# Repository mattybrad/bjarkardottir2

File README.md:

# Bjarkardóttir 2

A synthesizer/guitar hybrid. Somewhere between a MIDI guitar and a synthesizer. Not commercially viable. A time sink. A rabbit hole. An obsession. A mistake. An exercise in blind faith. A reason to tidy the shed. A sequel to a glass cannon.

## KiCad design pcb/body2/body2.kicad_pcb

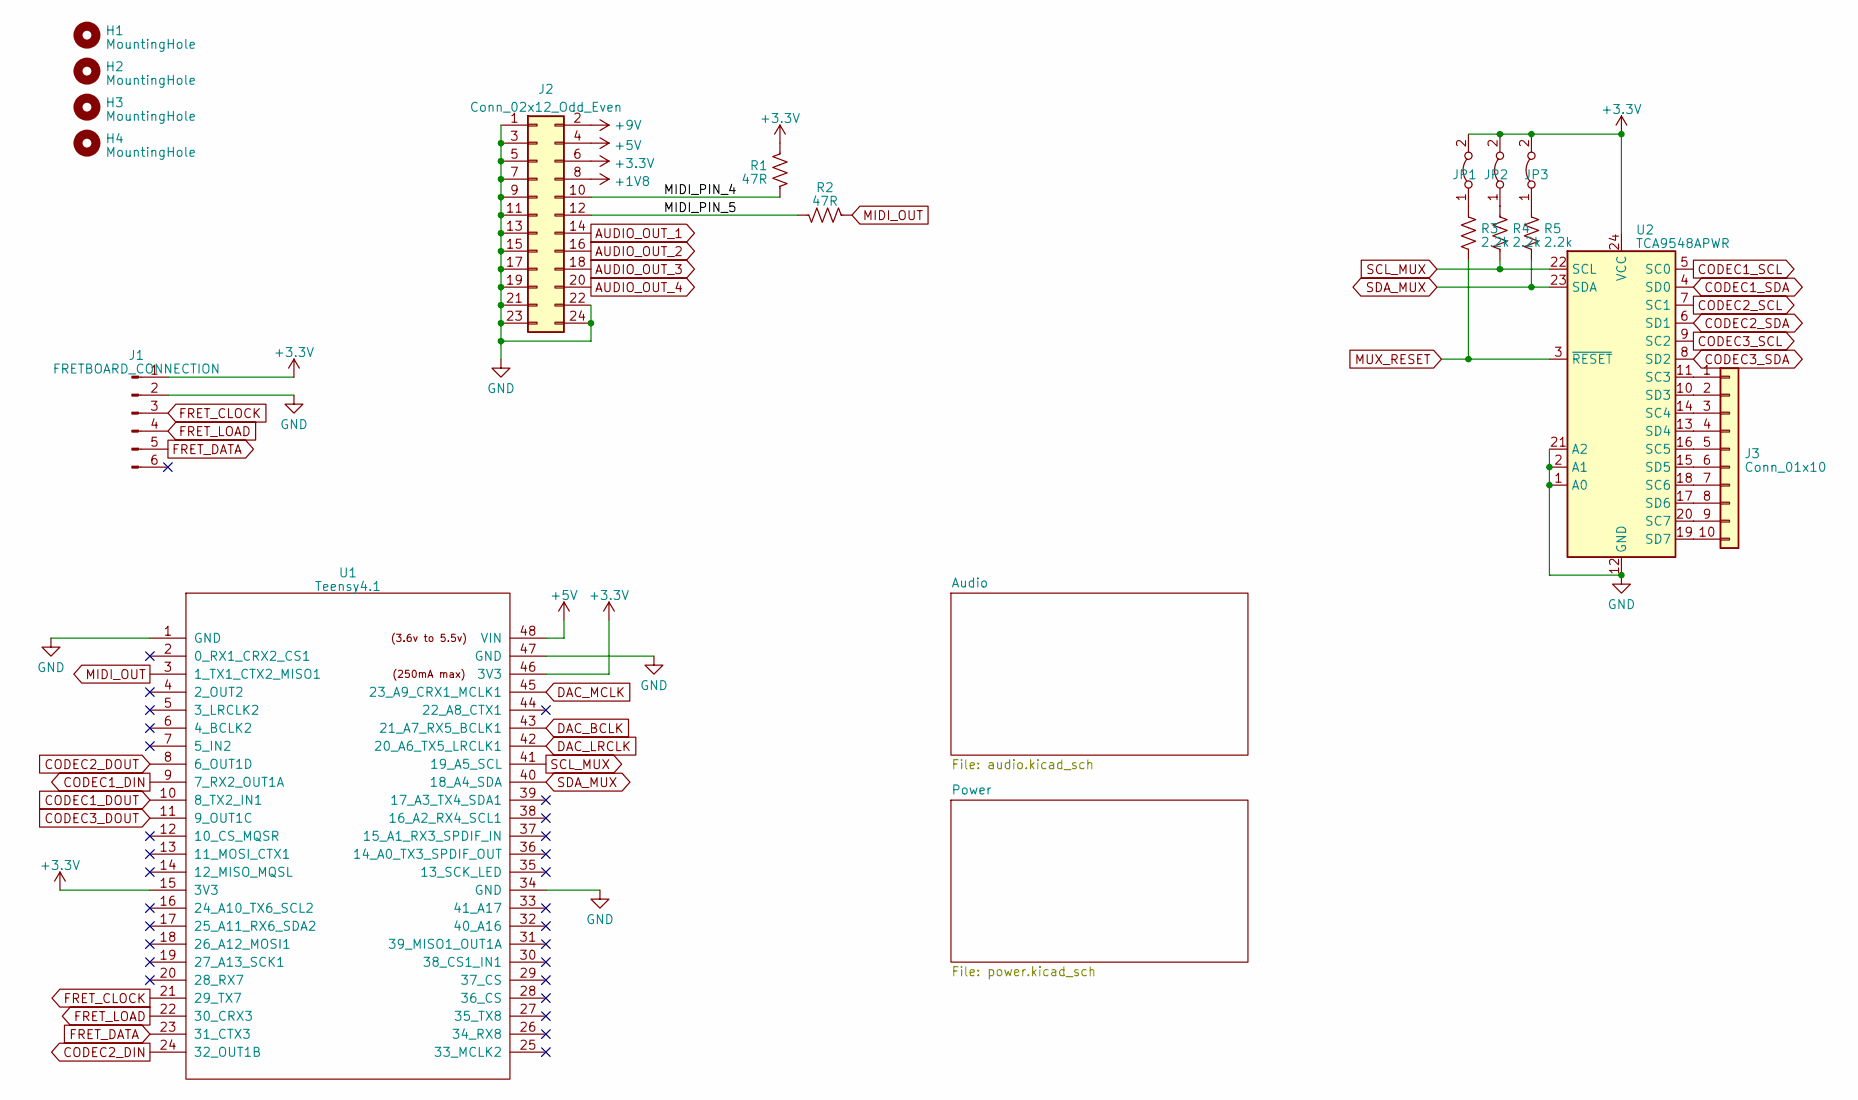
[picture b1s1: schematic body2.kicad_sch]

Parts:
H1, H2, H3, H4: MountingHole; MountingHole_3.2mm_M3
J1: FRETBOARD_CONNECTION; jst zh fretboard connector; LCSC C485355
J2: Conn_02x12_Odd_Even; PinHeader_2x12_P2.54mm_Vertical
J3: Conn_01x10; PinHeader_1x10_P1.27mm_Vertical
JP1, JP2, JP3: Jumper_2_Bridged; SolderJumper-2_P1.3mm_Bridged_Pad1.0x1.5mm
R1, R2: 47R; R_0603_1608Metric; LCSC C23182
R3, R4, R5: 2.2k; R_0603_1608Metric; LCSC C21190
U1: Teensy4.1; Teensy41_breakout
U2: TCA9548APWR; TSSOP-24_4.4x7.8mm_P0.65mm

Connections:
+1V8: J2.8; also elsewhere on the board
+3.3V: J1.1, J2.6, JP1.2 (B), JP2.2 (B), JP3.2 (B), R1.1, U1.15 (3V3), U1.46 (3V3), U2.24 (VCC); also elsewhere on the board
+5V: J2.4, U1.48 (VIN); also elsewhere on the board
+9V: J2.2; also elsewhere on the board
/MIDI_PIN_4: J2.10, R1.2
/MIDI_PIN_5: J2.12, R2.2
AUDIO_OUT_1: J2.14; also elsewhere on the board
AUDIO_OUT_2: J2.16; also elsewhere on the board
AUDIO_OUT_3: J2.18; also elsewhere on the board
AUDIO_OUT_4: J2.20; also elsewhere on the board
CODEC1_DIN: U1.9 (7_RX2_OUT1A); also elsewhere on the board
CODEC1_DOUT: U1.10 (8_TX2_IN1); also elsewhere on the board
CODEC1_SCL: U2.5 (SC0); also elsewhere on the board
CODEC1_SDA: U2.4 (SD0); also elsewhere on the board
CODEC2_DIN: U1.24 (32_OUT1B); also elsewhere on the board
CODEC2_DOUT: U1.8 (6_OUT1D); also elsewhere on the board
CODEC2_SCL: U2.7 (SC1); also elsewhere on the board
CODEC2_SDA: U2.6 (SD1); also elsewhere on the board
CODEC3_DOUT: U1.11 (9_OUT1C); also elsewhere on the board
CODEC3_SCL: U2.9 (SC2); also elsewhere on the board
CODEC3_SDA: U2.8 (SD2); also elsewhere on the board
DAC_BCLK: U1.43 (21_A7_RX5_BCLK1); also elsewhere on the board
DAC_LRCLK: U1.42 (20_A6_TX5_LRCLK1); also elsewhere on the board
DAC_MCLK: U1.45 (23_A9_CRX1_MCLK1); also elsewhere on the board
FRET_CLOCK: J1.3, U1.21 (29_TX7)
FRET_DATA: J1.5, U1.23 (31_CTX3)
FRET_LOAD: J1.4, U1.22 (30_CRX3)
GND: J1.2, J2.1, J2.3, J2.5, J2.7, J2.9, J2.11, J2.13, J2.15, J2.17, J2.19, J2.21, J2.22, J2.23, J2.24, U1.1 (GND), U1.34 (GND), U1.47 (GND), U2.1 (A0), U2.2 (A1), U2.12 (GND), U2.21 (A2); also elsewhere on the board
MIDI_OUT: R2.1, U1.3 (1_TX1_CTX2_MISO1)
MUX_RESET: R3.1, U2.3 (~RESET)
unnamed: J3.1, U2.11 (SC3)
unnamed: J3.2, U2.10 (SD3)
unnamed: J3.3, U2.14 (SC4)
unnamed: J3.4, U2.13 (SD4)
unnamed: J3.5, U2.16 (SC5)
unnamed: J3.6, U2.15 (SD5)
unnamed: J3.7, U2.18 (SC6)
unnamed: J3.8, U2.17 (SD6)
unnamed: J3.9, U2.20 (SC7)
unnamed: J3.10, U2.19 (SD7)
unnamed: JP1.1 (A), R3.2
unnamed: JP2.1 (A), R4.2
unnamed: JP3.1 (A), R5.2
SCL_MUX: R4.1, U1.41 (19_A5_SCL), U2.22 (SCL)
SDA_MUX: R5.1, U1.40 (18_A4_SDA), U2.23 (SDA)

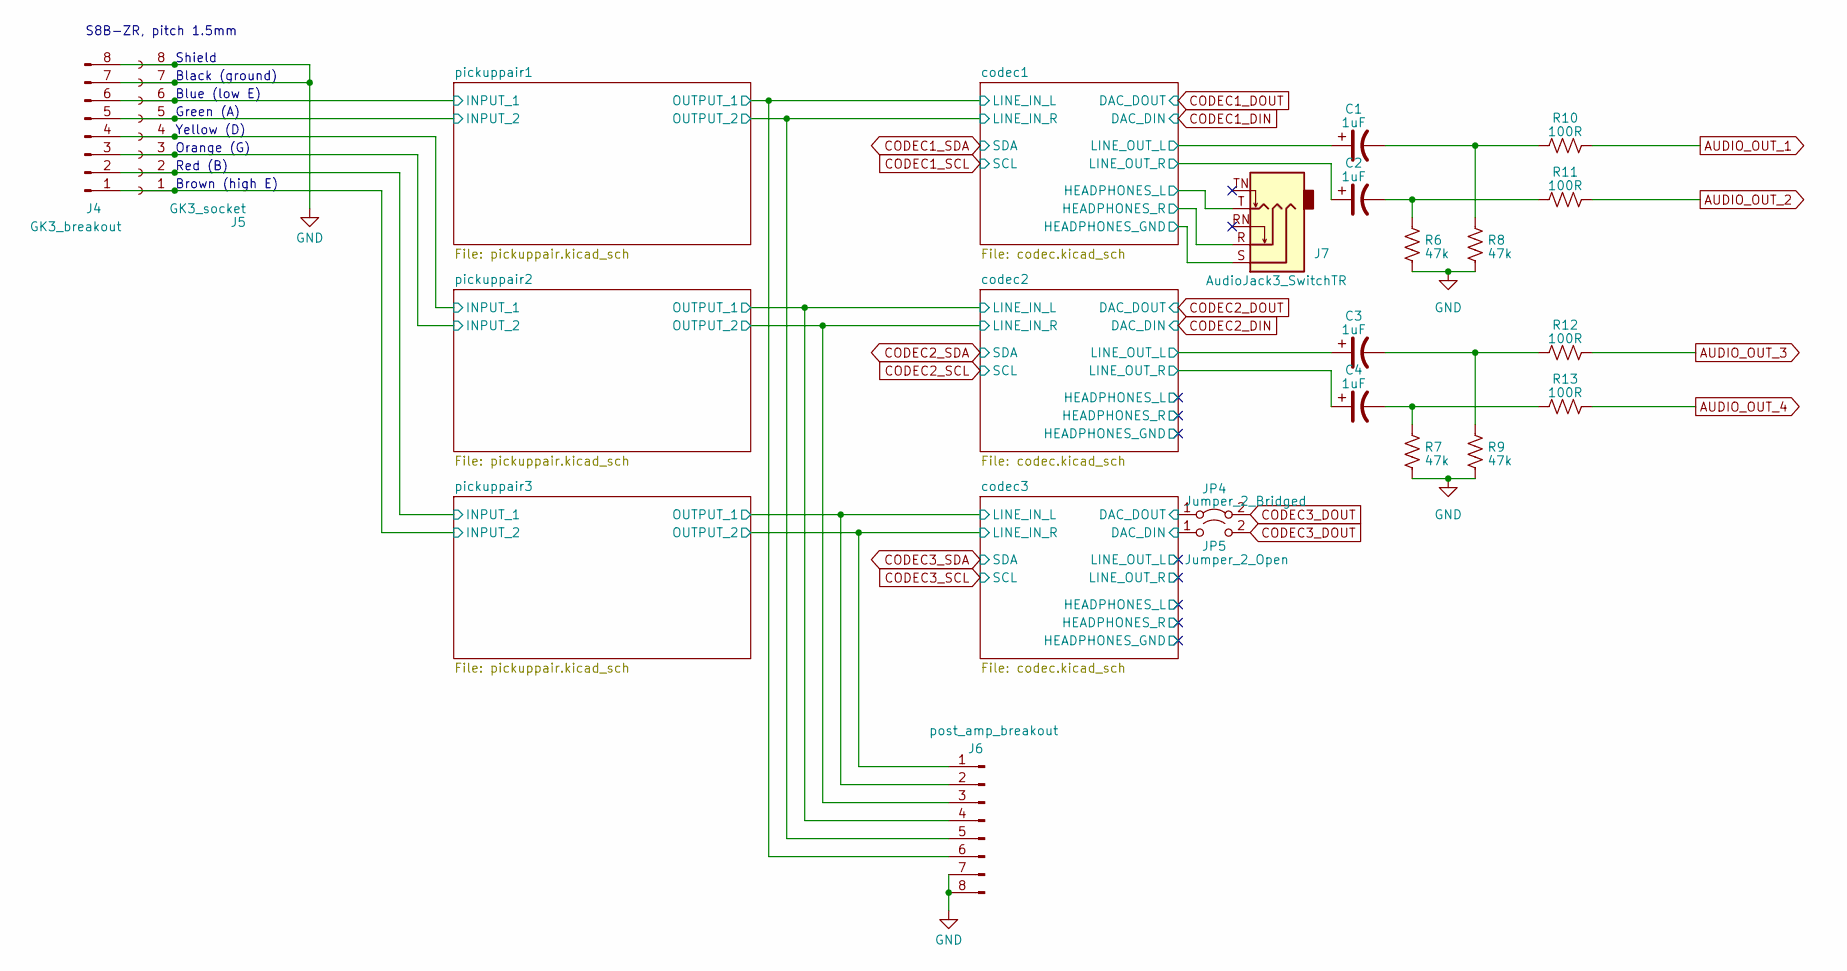
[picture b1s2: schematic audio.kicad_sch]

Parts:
C1, C3: 1uF; C_0603_1608Metric; LCSC C23630
C2, C4: 1uF; C_0603_1608Metric; LCSC C513735
J4: GK3_breakout; PinHeader_1x08_P2.54mm_Vertical
J5: GK3_socket; gk3 connector THT
J6: post_amp_breakout; PinHeader_1x08_P2.54mm_Vertical
J7: AudioJack3_SwitchTR; Jack_3.5mm_CUI_SJ1-3525N_Horizontal
JP4: Jumper_2_Bridged; SolderJumper-2_P1.3mm_Bridged_Pad1.0x1.5mm
JP5: Jumper_2_Open; SolderJumper-2_P1.3mm_Open_Pad1.0x1.5mm
R6, R7: 47k; R_0603_1608Metric; LCSC C22935
R8, R9: 47k; R_0603_1608Metric; LCSC C22976
R10, R11, R12, R13: 100R; R_0603_1608Metric; LCSC C22976

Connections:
/Audio/codec1/HEADPHONES_GND: J7.S; also elsewhere on the board
/Audio/codec1/HEADPHONES_L: J7.T; also elsewhere on the board
/Audio/codec1/HEADPHONES_R: J7.R; also elsewhere on the board
/Audio/codec1/LINE_IN_L: J6.6; also elsewhere on the board
/Audio/codec1/LINE_IN_R: J6.5; also elsewhere on the board
/Audio/codec1/LINE_OUT_L: C1.1; also elsewhere on the board
/Audio/codec1/LINE_OUT_R: C2.1; also elsewhere on the board
/Audio/codec2/LINE_IN_L: J6.4; also elsewhere on the board
/Audio/codec2/LINE_IN_R: J6.3; also elsewhere on the board
/Audio/codec2/LINE_OUT_L: C3.1; also elsewhere on the board
/Audio/codec2/LINE_OUT_R: C4.1; also elsewhere on the board
/Audio/codec3/DAC_DIN: JP5.1 (A); also elsewhere on the board
/Audio/codec3/DAC_DOUT: JP4.1 (A); also elsewhere on the board
/Audio/codec3/LINE_IN_L: J6.2; also elsewhere on the board
/Audio/codec3/LINE_IN_R: J6.1; also elsewhere on the board
/Audio/pickuppair1/INPUT_1: J4.6, J5.6; also elsewhere on the board
/Audio/pickuppair1/INPUT_2: J4.5, J5.5; also elsewhere on the board
/Audio/pickuppair2/INPUT_1: J4.4, J5.4; also elsewhere on the board
/Audio/pickuppair2/INPUT_2: J4.3, J5.3; also elsewhere on the board
/Audio/pickuppair3/INPUT_1: J4.2, J5.2; also elsewhere on the board
/Audio/pickuppair3/INPUT_2: J4.1, J5.1; also elsewhere on the board
AUDIO_OUT_1: R10.1; also elsewhere on the board
AUDIO_OUT_2: R11.1; also elsewhere on the board
AUDIO_OUT_3: R12.1; also elsewhere on the board
AUDIO_OUT_4: R13.1; also elsewhere on the board
CODEC3_DOUT: JP4.2 (B), JP5.2 (B); also elsewhere on the board
GND: J4.7, J4.8, J5.7, J5.8, J6.7, J6.8, R6.1, R7.1, R8.1, R9.1; also elsewhere on the board
unnamed: C1.2, R8.2, R10.2
unnamed: C2.2, R6.2, R11.2
unnamed: C3.2, R9.2, R12.2
unnamed: C4.2, R7.2, R13.2

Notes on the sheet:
Black (ground)
Yellow (D)
Brown (high E)
Red (B)
Green (A)
Orange (G)
S8B-ZR, pitch 1.5mm
Blue (low E)
Shield

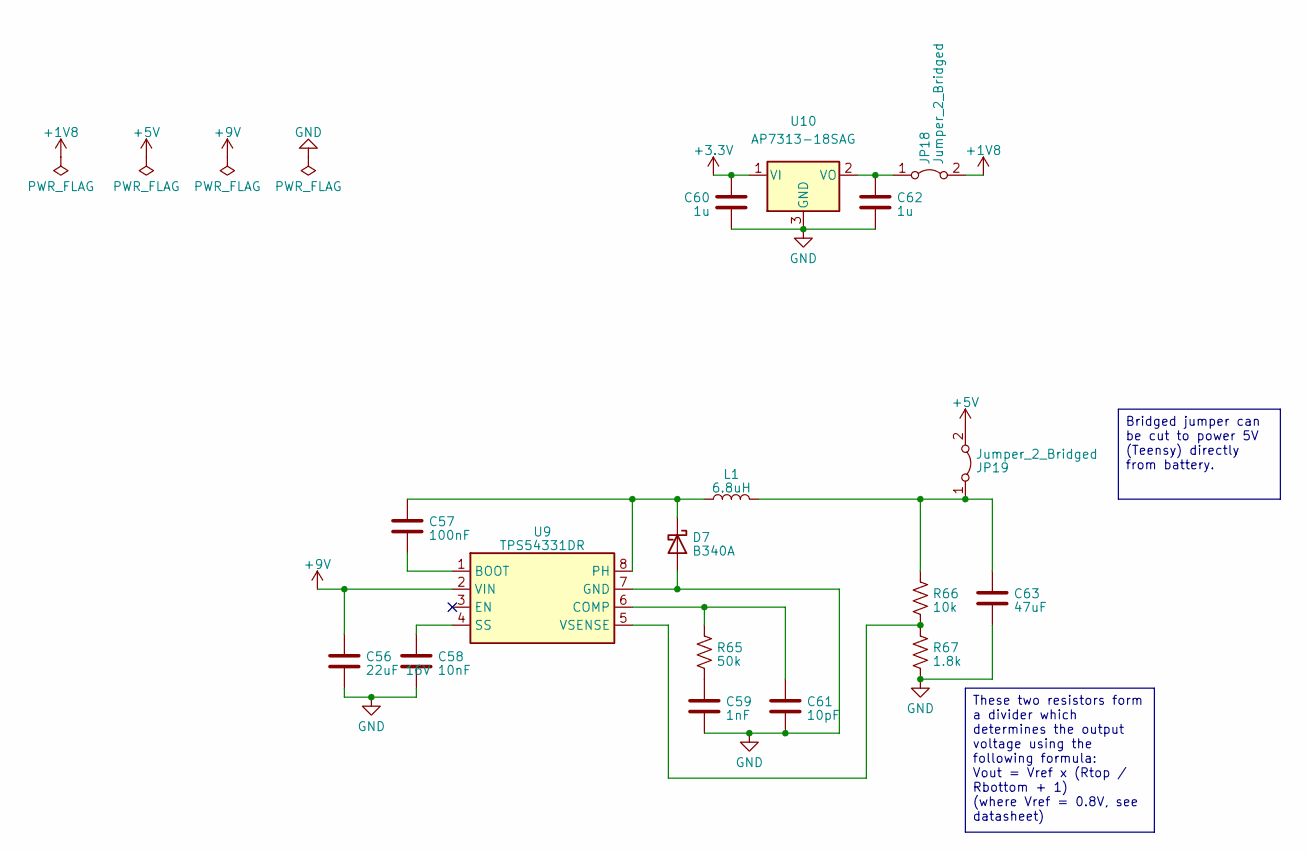
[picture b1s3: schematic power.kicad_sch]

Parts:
C56: 22uF 16V; C_0805_2012Metric
C57: 100nF; C_0603_1608Metric
C58: 10nF; C_0603_1608Metric
C59: 1nF; C_0603_1608Metric
C60, C62: 1u; C_0603_1608Metric
C61: 10pF; C_0603_1608Metric
C63: 47uF; C_1210_3225Metric
D7: B340A; D_SMA
JP18, JP19: Jumper_2_Bridged; SolderJumper-2_P1.3mm_Bridged_Pad1.0x1.5mm
L1: 6.8uH; L_Changjiang_FNR4020S
R65: 50k; R_0603_1608Metric
R66: 10k; R_0603_1608Metric
R67: 1.8k; R_0603_1608Metric
U9: TPS54331DR; SOIC-8_3.9x4.9mm_P1.27mm
U10: AP7313-18SAG; SOT-23

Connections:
+1V8: JP18.2 (B); also elsewhere on the board
+3.3V: C60.1, U10.1 (VI); also elsewhere on the board
+5V: JP19.2 (B); also elsewhere on the board
+9V: C56.1, U9.2 (VIN); also elsewhere on the board
GND: C56.2, C58.2, C59.2, C60.2, C61.2, C62.2, C63.2, D7.2 (A), R67.2, U9.7 (GND), U10.3 (GND); also elsewhere on the board
unnamed: C59.1, R65.2
unnamed: C57.1, D7.1 (K), L1.1, U9.8 (PH)
unnamed: C62.1, JP18.1 (A), U10.2 (VO)
unnamed: C63.1, JP19.1 (A), L1.2, R66.1
unnamed: C57.2, U9.1 (BOOT)
unnamed: C61.1, R65.1, U9.6 (COMP)
unnamed: C58.1, U9.4 (SS)
unnamed: R66.2, R67.1, U9.5 (VSENSE)

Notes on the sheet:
Bridged jumper can be cut to power 5V (Teensy) directly from battery.
These two resistors form a divider which determines the output voltage using the following formula: Vout = Vref x (Rtop / Rbottom + 1) (where Vref = 0.8V, see datasheet)

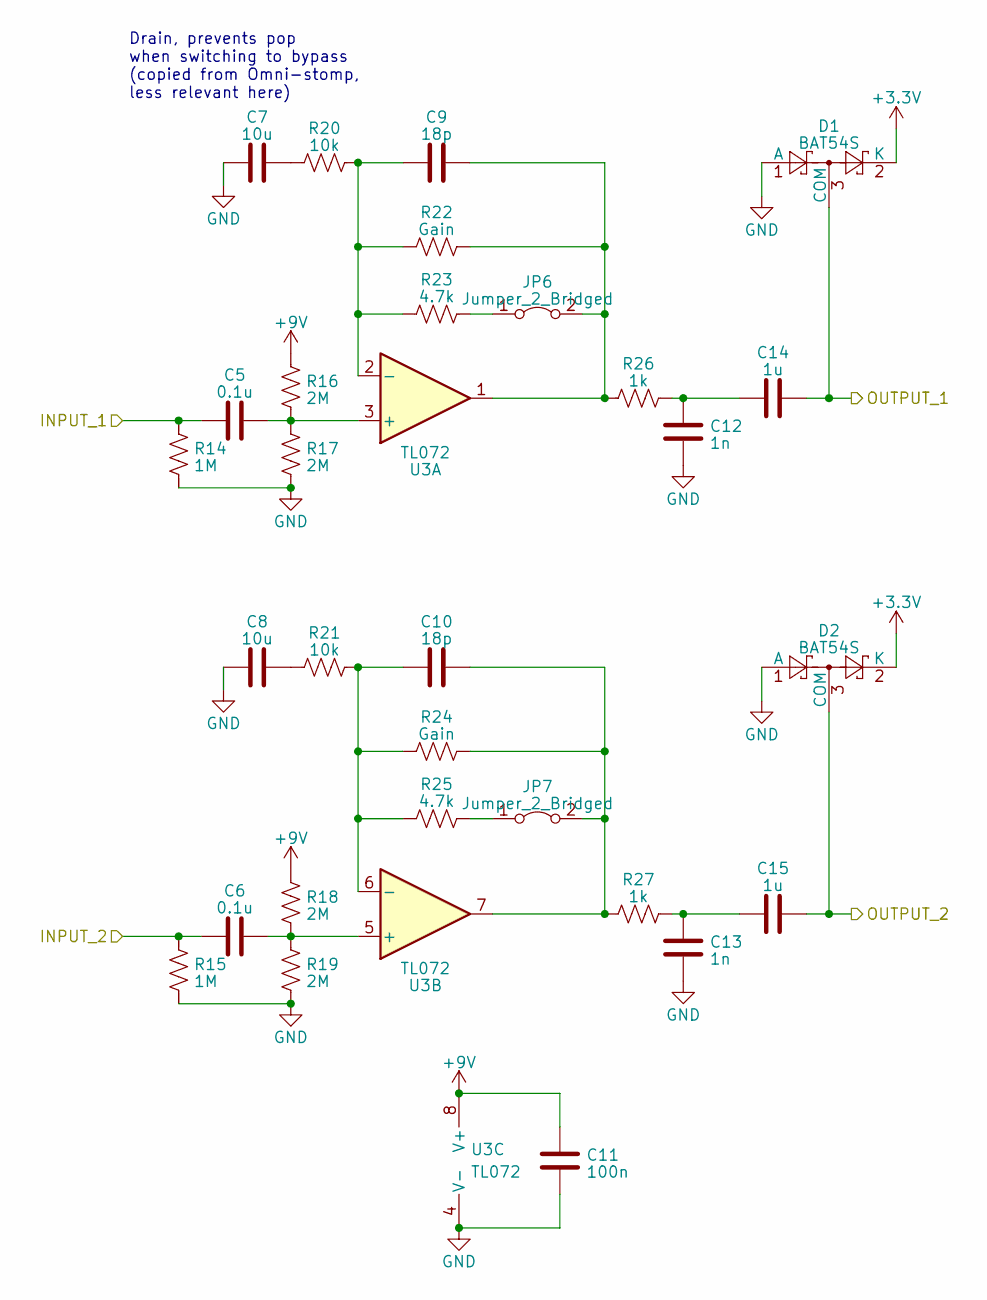
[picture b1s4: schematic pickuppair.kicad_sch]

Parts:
C5, C6: 0.1u; C_0603_1608Metric
C7, C8: 10u; C_0603_1608Metric
C9, C10: 18p; C_0603_1608Metric
C11: 100n; C_0603_1608Metric
C12, C13: 1n; C_0603_1608Metric
C14, C15: 1u; C_0603_1608Metric
D1, D2: BAT54S; SOT-23
JP6, JP7: Jumper_2_Bridged; SolderJumper-2_P1.3mm_Bridged_Pad1.0x1.5mm
R14, R15: 1M; R_0603_1608Metric
R16, R17, R18, R19: 2M; R_0603_1608Metric
R20, R21: 10k; R_0603_1608Metric
R22, R24: Gain; R_Axial_DIN0207_L6.3mm_D2.5mm_P7.62mm_Horizontal
R23, R25: 4.7k; R_0603_1608Metric
R26, R27: 1k; R_0603_1608Metric
U3: TL072; SOIC-8_3.9x4.9mm_P1.27mm

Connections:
+3.3V: D1.2 (K), D2.2 (K); also elsewhere on the board
+9V: C11.2, R16.1, R18.1, U3.8 (V+); also elsewhere on the board
/Audio/codec1/LINE_IN_L: C14.1, D1.3 (COM); also elsewhere on the board
/Audio/codec1/LINE_IN_R: C15.1, D2.3 (COM); also elsewhere on the board
/Audio/pickuppair1/INPUT_1: C5.1, R14.1; also elsewhere on the board
/Audio/pickuppair1/INPUT_2: C6.1, R15.1; also elsewhere on the board
GND: C7.1, C8.1, C11.1, C12.2, C13.2, D1.1 (A), D2.1 (A), R14.2, R15.2, R17.2, R19.2, U3.4 (V-); also elsewhere on the board
unnamed: C7.2, R20.1
unnamed: C8.2, R21.1
unnamed: C12.1, C14.2, R26.2
unnamed: C13.1, C15.2, R27.2
unnamed: JP6.1 (A), R23.2
unnamed: C9.2, JP6.2 (B), R22.2, R26.1, U3.1
unnamed: JP7.1 (A), R25.2
unnamed: C10.2, JP7.2 (B), R24.2, R27.1, U3.7
unnamed: C5.2, R16.2, R17.1, U3.3 (+)
unnamed: C9.1, R20.2, R22.1, R23.1, U3.2 (-)
unnamed: C6.2, R18.2, R19.1, U3.5 (+)
unnamed: C10.1, R21.2, R24.1, R25.1, U3.6 (-)

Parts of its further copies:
C18, C19, C29, C30: 10u; C_0603_1608Metric
C20, C21, C31, C32: 18p; C_0603_1608Metric
C22, C33: 100n; C_0603_1608Metric
C23, C24, C34, C35: 1n; C_0603_1608Metric
C25, C26, C36, C37: 1u; C_0603_1608Metric
C27, C28: 0.1u; C_0603_1608Metric
D3, D4, D5, D6: BAT54S; SOT-23
JP8, JP9, JP10, JP11: Jumper_2_Bridged; SolderJumper-2_P1.3mm_Bridged_Pad1.0x1.5mm
R28, R29, R42, R43: 1M; R_0603_1608Metric
R30, R31, R32, R33, R44, R45, R46, R47: 2M; R_0603_1608Metric
R34, R35, R48, R49: 10k; R_0603_1608Metric
R36, R38, R50, R52: Gain; R_Axial_DIN0207_L6.3mm_D2.5mm_P7.62mm_Horizontal
R37, R39, R51, R53: 4.7k; R_0603_1608Metric
R40, R41, R54, R55: 1k; R_0603_1608Metric
U4, U5: TL072; SOIC-8_3.9x4.9mm_P1.27mm

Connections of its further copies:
+3.3V: D3.2 (K), D4.2 (K), D5.2 (K), D6.2 (K); also elsewhere on the board
+9V: C22.2, C33.2, R30.1, R32.1, R44.1, R46.1, U4.8 (V+), U5.8 (V+); also elsewhere on the board
/Audio/codec2/LINE_IN_L: C25.1, D3.3 (COM); also elsewhere on the board
/Audio/codec2/LINE_IN_R: C26.1, D4.3 (COM); also elsewhere on the board
/Audio/codec3/LINE_IN_L: C36.1, D5.3 (COM); also elsewhere on the board
/Audio/codec3/LINE_IN_R: C37.1, D6.3 (COM); also elsewhere on the board
/Audio/pickuppair2/INPUT_1: R28.1; also elsewhere on the board
/Audio/pickuppair2/INPUT_2: R29.1; also elsewhere on the board
/Audio/pickuppair3/INPUT_1: C27.1, R42.1; also elsewhere on the board
/Audio/pickuppair3/INPUT_2: C28.1, R43.1; also elsewhere on the board
GND: C18.1, C19.1, C22.1, C23.2, C24.2, C29.1, C30.1, C33.1, C34.2, C35.2, D3.1 (A), D4.1 (A), D5.1 (A), D6.1 (A), R28.2, R29.2, R31.2, R33.2, R42.2, R43.2, R45.2, R47.2, U4.4 (V-), U5.4 (V-); also elsewhere on the board
unnamed: C18.2, R34.1
unnamed: C19.2, R35.1
unnamed: C23.1, C25.2, R40.2
unnamed: C24.1, C26.2, R41.2
unnamed: C29.2, R48.1
unnamed: C30.2, R49.1
unnamed: C34.1, C36.2, R54.2
unnamed: C35.1, C37.2, R55.2
unnamed: JP8.1 (A), R37.2
unnamed: C20.2, JP8.2 (B), R36.2, R40.1, U4.1
unnamed: JP9.1 (A), R39.2
unnamed: C21.2, JP9.2 (B), R38.2, R41.1, U4.7
unnamed: JP10.1 (A), R51.2
unnamed: C31.2, JP10.2 (B), R50.2, R54.1, U5.1
unnamed: JP11.1 (A), R53.2
unnamed: C32.2, JP11.2 (B), R52.2, R55.1, U5.7
unnamed 114: R30.2, R31.1, U4.3 (+); also elsewhere on the board
unnamed: C20.1, R34.2, R36.1, R37.1, U4.2 (-)
unnamed 116: R32.2, R33.1, U4.5 (+); also elsewhere on the board
unnamed: C21.1, R35.2, R38.1, R39.1, U4.6 (-)
unnamed: C27.2, R44.2, R45.1, U5.3 (+)
unnamed: C31.1, R48.2, R50.1, R51.1, U5.2 (-)
unnamed: C28.2, R46.2, R47.1, U5.5 (+)
unnamed: C32.1, R49.2, R52.1, R53.1, U5.6 (-)

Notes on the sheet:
Drain, prevents pop when switching to bypass (copied from Omni-stomp, less relevant here)

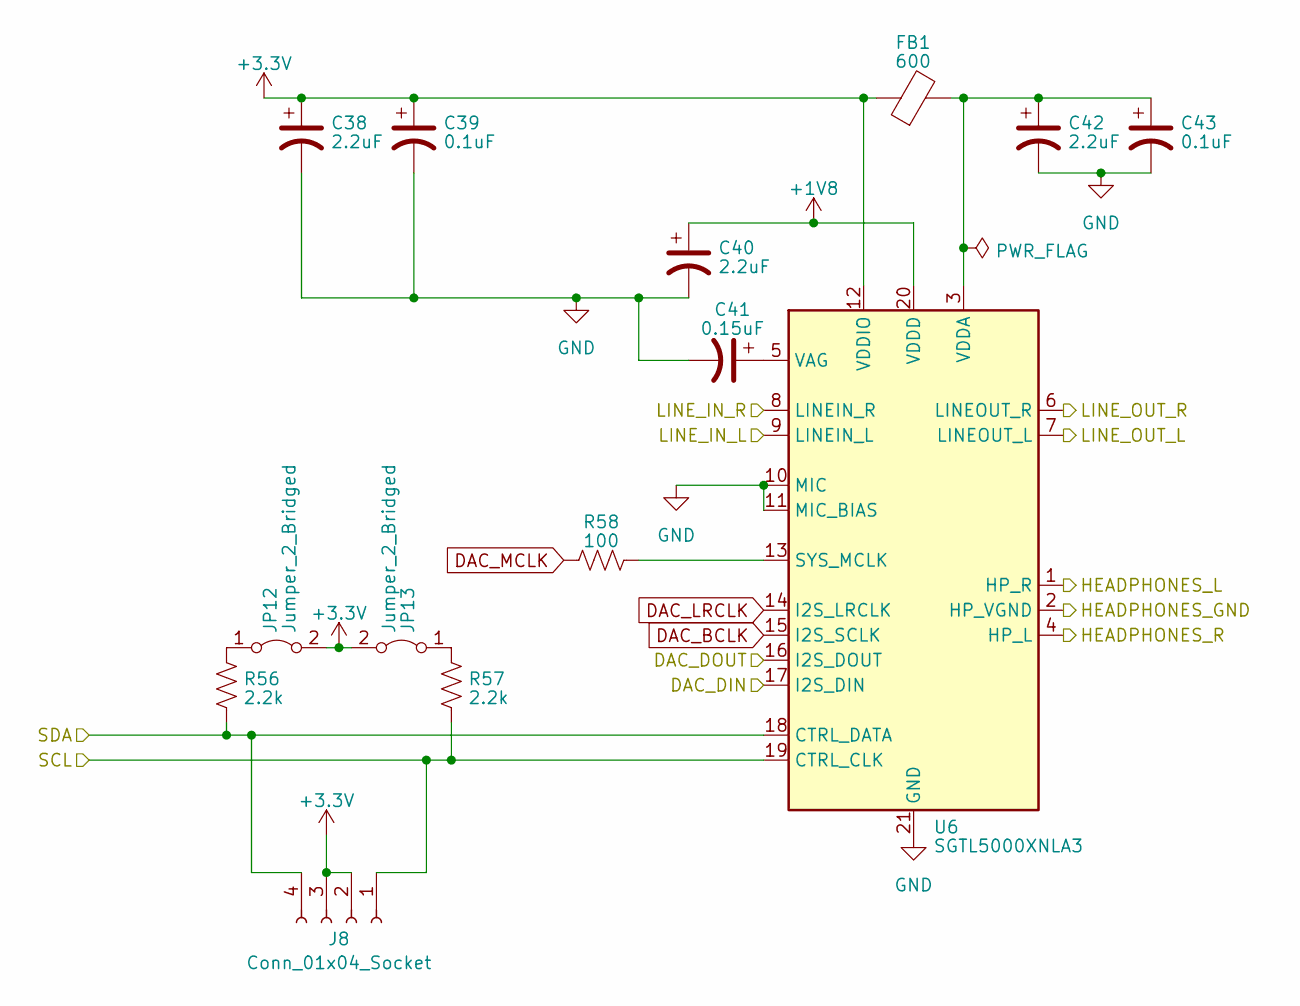
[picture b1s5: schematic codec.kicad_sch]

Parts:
C38, C40, C42: 2.2uF; C_0603_1608Metric
C39, C43: 0.1uF; C_0603_1608Metric
C41: 0.15uF; C_0603_1608Metric
FB1: 600; L_0603_1608Metric
J8: Conn_01x04_Socket; PinSocket_1x04_P1.27mm_Vertical
JP12, JP13: Jumper_2_Bridged; SolderJumper-2_P1.3mm_Bridged_Pad1.0x1.5mm
R56, R57: 2.2k; R_0603_1608Metric; LCSC C21190
R58: 100; R_0603_1608Metric
U6: SGTL5000XNLA3; QFN-20-1EP_3x3mm_P0.4mm_EP1.65x1.65mm

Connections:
+1V8: C40.1, U6.20 (VDDD); also elsewhere on the board
+3.3V: C38.1, C39.1, FB1.1, J8.2, J8.3, JP12.2 (B), JP13.2 (B), U6.12 (VDDIO); also elsewhere on the board
/Audio/codec1/HEADPHONES_GND: U6.2 (HP_VGND); also elsewhere on the board
/Audio/codec1/HEADPHONES_L: U6.1 (HP_R); also elsewhere on the board
/Audio/codec1/HEADPHONES_R: U6.4 (HP_L); also elsewhere on the board
/Audio/codec1/LINE_IN_L: U6.9 (LINEIN_L); also elsewhere on the board
/Audio/codec1/LINE_IN_R: U6.8 (LINEIN_R); also elsewhere on the board
/Audio/codec1/LINE_OUT_L: U6.7 (LINEOUT_L); also elsewhere on the board
/Audio/codec1/LINE_OUT_R: U6.6 (LINEOUT_R); also elsewhere on the board
CODEC1_DIN: U6.17 (I2S_DIN); also elsewhere on the board
CODEC1_DOUT: U6.16 (I2S_DOUT); also elsewhere on the board
CODEC1_SCL: J8.1, R57.1, U6.19 (CTRL_CLK); also elsewhere on the board
CODEC1_SDA: J8.4, R56.1, U6.18 (CTRL_DATA); also elsewhere on the board
DAC_BCLK: U6.15 (I2S_SCLK); also elsewhere on the board
DAC_LRCLK: U6.14 (I2S_LRCLK); also elsewhere on the board
DAC_MCLK: R58.2; also elsewhere on the board
GND: C38.2, C39.2, C40.2, C41.2, C42.2, C43.2, U6.10 (MIC), U6.11 (MIC_BIAS), U6.21 (GND); also elsewhere on the board
unnamed: JP12.1 (A), R56.2
unnamed: JP13.1 (A), R57.2
unnamed: R58.1, U6.13 (SYS_MCLK)
unnamed: C41.1, U6.5 (VAG)
unnamed: C42.1, C43.1, FB1.2, U6.3 (VDDA)

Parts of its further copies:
C44, C46, C48, C50, C52, C54: 2.2uF; C_0603_1608Metric
C45, C49, C51, C55: 0.1uF; C_0603_1608Metric
C47, C53: 0.15uF; C_0603_1608Metric
FB2, FB3: 600; L_0603_1608Metric
J9, J10: Conn_01x04_Socket; PinSocket_1x04_P1.27mm_Vertical
JP14, JP15, JP16, JP17: Jumper_2_Bridged; SolderJumper-2_P1.3mm_Bridged_Pad1.0x1.5mm
R59, R60, R62, R63: 2.2k; R_0603_1608Metric; LCSC C21190
R61, R64: 100; R_0603_1608Metric
U7, U8: SGTL5000XNLA3; QFN-20-1EP_3x3mm_P0.4mm_EP1.65x1.65mm

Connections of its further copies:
+1V8: C46.1, C52.1, U7.20 (VDDD), U8.20 (VDDD); also elsewhere on the board
+3.3V: C44.1, C45.1, C50.1, C51.1, FB2.1, FB3.1, J9.2, J9.3, J10.2, J10.3, JP14.2 (B), JP15.2 (B), JP16.2 (B), JP17.2 (B), U7.12 (VDDIO), U8.12 (VDDIO); also elsewhere on the board
/Audio/codec2/HEADPHONES_GND: U7.2 (HP_VGND)
/Audio/codec2/HEADPHONES_L: U7.1 (HP_R)
/Audio/codec2/HEADPHONES_R: U7.4 (HP_L)
/Audio/codec2/LINE_IN_L: U7.9 (LINEIN_L); also elsewhere on the board
/Audio/codec2/LINE_IN_R: U7.8 (LINEIN_R); also elsewhere on the board
/Audio/codec2/LINE_OUT_L: U7.7 (LINEOUT_L); also elsewhere on the board
/Audio/codec2/LINE_OUT_R: U7.6 (LINEOUT_R); also elsewhere on the board
/Audio/codec3/DAC_DIN: U8.17 (I2S_DIN); also elsewhere on the board
/Audio/codec3/DAC_DOUT: U8.16 (I2S_DOUT); also elsewhere on the board
/Audio/codec3/HEADPHONES_GND: U8.2 (HP_VGND)
/Audio/codec3/HEADPHONES_L: U8.1 (HP_R)
/Audio/codec3/HEADPHONES_R: U8.4 (HP_L)
/Audio/codec3/LINE_IN_L: U8.9 (LINEIN_L); also elsewhere on the board
/Audio/codec3/LINE_IN_R: U8.8 (LINEIN_R); also elsewhere on the board
/Audio/codec3/LINE_OUT_L: U8.7 (LINEOUT_L)
/Audio/codec3/LINE_OUT_R: U8.6 (LINEOUT_R)
CODEC2_DIN: U7.17 (I2S_DIN); also elsewhere on the board
CODEC2_DOUT: U7.16 (I2S_DOUT); also elsewhere on the board
CODEC2_SCL: J9.1, R60.1, U7.19 (CTRL_CLK); also elsewhere on the board
CODEC2_SDA: J9.4, R59.1, U7.18 (CTRL_DATA); also elsewhere on the board
CODEC3_SCL: J10.1, R63.1, U8.19 (CTRL_CLK); also elsewhere on the board
CODEC3_SDA: J10.4, R62.1, U8.18 (CTRL_DATA); also elsewhere on the board
DAC_BCLK: U7.15 (I2S_SCLK), U8.15 (I2S_SCLK); also elsewhere on the board
DAC_LRCLK: U7.14 (I2S_LRCLK), U8.14 (I2S_LRCLK); also elsewhere on the board
DAC_MCLK: R61.2, R64.2; also elsewhere on the board
GND: C44.2, C45.2, C46.2, C47.2, C48.2, C49.2, C50.2, C51.2, C52.2, C53.2, C54.2, C55.2, U7.10 (MIC), U7.11 (MIC_BIAS), U7.21 (GND), U8.10 (MIC), U8.11 (MIC_BIAS), U8.21 (GND); also elsewhere on the board
unnamed: JP14.1 (A), R59.2
unnamed: JP15.1 (A), R60.2
unnamed: JP16.1 (A), R62.2
unnamed: JP17.1 (A), R63.2
unnamed: R61.1, U7.13 (SYS_MCLK)
unnamed: C47.1, U7.5 (VAG)
unnamed: C48.1, C49.1, FB2.2, U7.3 (VDDA)
unnamed: R64.1, U8.13 (SYS_MCLK)
unnamed: C53.1, U8.5 (VAG)
unnamed: C54.1, C55.1, FB3.2, U8.3 (VDDA)

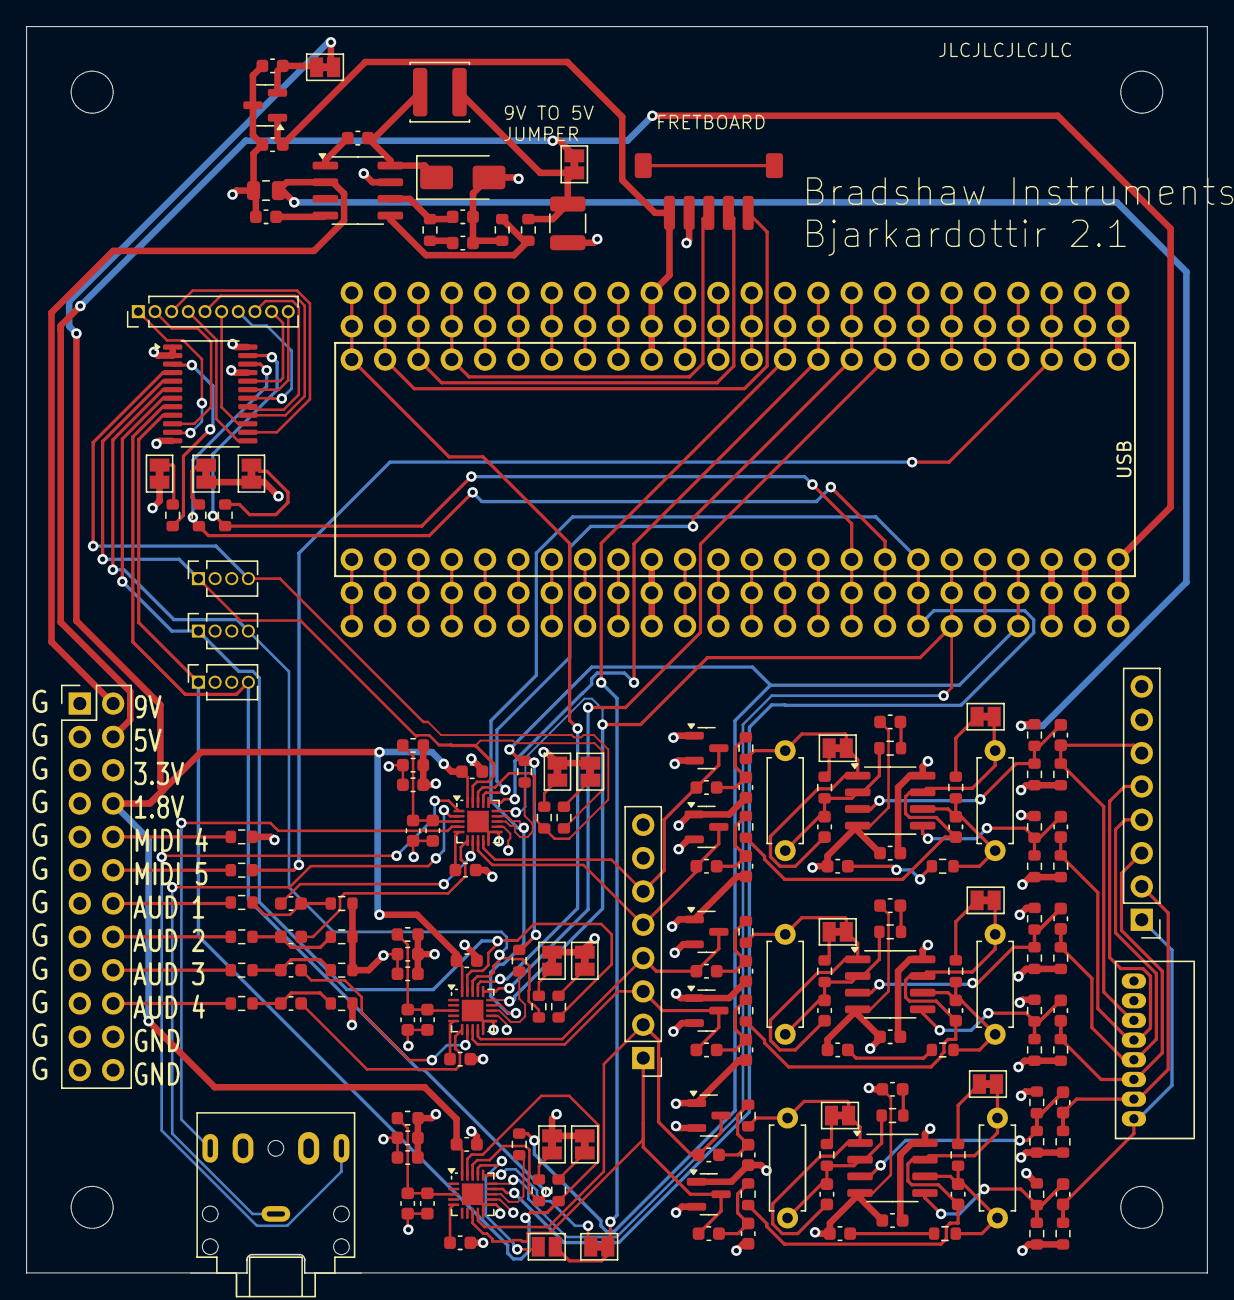
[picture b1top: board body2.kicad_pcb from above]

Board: 4 copper layers, 90.0 x 95.0 mm, 184 parts (0 on the bottom side), 129 nets.

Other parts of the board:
C16, C17: 0.1u; C_0603_1608Metric

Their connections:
/Audio/pickuppair2/INPUT_1: C16.1; also elsewhere on the board
/Audio/pickuppair2/INPUT_2: C17.1; also elsewhere on the board
unnamed 114: C16.2; also elsewhere on the board
unnamed 116: C17.2; also elsewhere on the board

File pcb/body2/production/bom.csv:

Designator,Footprint,Quantity,Value,LCSC Part #
"C1, C3",0603,2,1uF,C23630
"C10, C20, C21, C31, C32, C9",0603,6,18p,
"C11, C22, C33",0603,3,100n,
"C12, C13, C23, C24, C34, C35",0603,6,1n,
"C14, C15, C25, C26, C36, C37, C60, C62",0603,8,1u,
"C16, C17, C27, C28, C5, C6",0603,6,0.1u,
"C18, C19, C29, C30, C7, C8",0603,6,10u,
"C2, C4",0603,2,1uF,C513735
"C38, C40, C42, C44, C46, C48, C50, C52, C54",0603,9,2.2uF,
"C39, C43, C45, C49, C51, C55",0603,6,0.1uF,
"C41, C47, C53",0603,3,0.15uF,
C56,0805,1,22uF 16V,
C57,0603,1,100nF,
C58,0603,1,10nF,
C59,0603,1,1nF,
C61,0603,1,10pF,
C63,1210,1,47uF,
"D1, D2, D3, D4, D5, D6",SOT-23,6,BAT54S,
D7,D_SMA,1,B340A,
"FB1, FB2, FB3",0603,3,600,
"H1, H2, H3, H4",MountingHole_3.2mm_M3,4,MountingHole,
J1,jst zh fretboard connector,1,FRETBOARD_CONNECTION,C485355
"J10, J8, J9",PinSocket_1x04_P1.27mm_Vertical,3,Conn_01x04_Socket,
J2,PinHeader_2x12_P2.54mm_Vertical,1,Conn_02x12_Odd_Even,
J3,PinHeader_1x10_P1.27mm_Vertical,1,Conn_01x10,
J4,PinHeader_1x08_P2.54mm_Vertical,1,GK3_breakout,
J5,gk3 connector THT,1,GK3_socket,
J6,PinHeader_1x08_P2.54mm_Vertical,1,post_amp_breakout,
J7,Jack_3.5mm_CUI_SJ1-3525N_Horizontal,1,AudioJack3_SwitchTR,
"JP1, JP10, JP11, JP12, JP13, JP14, JP15, JP16, JP17, JP18, JP19, JP2, JP3, JP4, JP6, JP7, JP8, JP9",SolderJumper-2_P1.3mm_Bridged_Pad1.0x1.5mm,18,Jumper_2_Bridged,
JP5,SolderJumper-2_P1.3mm_Open_Pad1.0x1.5mm,1,Jumper_2_Open,
L1,L_Changjiang_FNR4020S,1,6.8uH,
"R1, R2",0603,2,47R,C23182
"R10, R11, R12, R13",0603,4,100R,C22976
"R14, R15, R28, R29, R42, R43",0603,6,1M,
"R16, R17, R18, R19, R30, R31, R32, R33, R44, R45, R46, R47",0603,12,2M,
"R20, R21, R34, R35, R48, R49, R66",0603,7,10k,
"R22, R24, R36, R38, R50, R52",R_Axial_DIN0207_L6.3mm_D2.5mm_P7.62mm_Horizontal,6,Gain,
"R23, R25, R37, R39, R51, R53",0603,6,4.7k,
"R26, R27, R40, R41, R54, R55",0603,6,1k,
"R3, R4, R5, R56, R57, R59, R60, R62, R63",0603,9,2.2k,C21190
"R58, R61, R64",0603,3,100,
"R6, R7",0603,2,47k,C22935
R65,0603,1,50k,
R67,0603,1,1.8k,
"R8, R9",0603,2,47k,C22976
U1,Teensy41_breakout,1,Teensy4.1,
U10,SOT-23,1,AP7313-18SAG,
U2,TSSOP-24_4.4x7.8mm_P0.65mm,1,TCA9548APWR,
"U3, U4, U5",SOIC-8_3.9x4.9mm_P1.27mm,3,TL072,
"U6, U7, U8",QFN-20-1EP_3x3mm_P0.4mm_EP1.65x1.65mm,3,SGTL5000XNLA3,
U9,SOIC-8_3.9x4.9mm_P1.27mm,1,TPS54331DR,
